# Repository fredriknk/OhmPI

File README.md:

# OhmPi

Development of a low-cost multi-electrodes resistivity meter for electrical resistivity mesaurement for lab applications, based on raspberry board

## Installation

All dependencies are specified in *requirements.txt*

**Note:** all instructions below should be typed in the terminal

It is first necessary to create an OhmPi virtual environment and install all dependancies
`.create_ohmpi_virtual_envrinment.sh`

When the installation is completed check that requirements are met using 
`pip list`

We strongly recommend users to create a virtual environment to run the code and installed all required dependencies:
*  activate it using the following command:
   `source ohmpy/bin/activate`
*  you should run you code within the virtual environment
*  to leave the virtual environment simply type: `deactivate`

## First run with four electrodes

In the examples folder, you will find the code "simple_measurement.py".

Running this code, in Thonny (IDE) or in the terminal, will allow you to make a simple 4 electrodes measurement A B M N.

## Citing Ohmpi

If you use Ohmpi for you work, please cite [this paper](https://www.sciencedirect.com/science/article/pii/S2468067220300316) as:

    Rémi Clement, Yannick Fargier, Vivien Dubois, Julien Gance, Emile Gros, Nicolas Forquet, OhmPi: An open source data logger for 
    dedicated applications of electrical resistivity imaging at the small and laboratory scale, HardwareX, Volume 8, 2020, e00122, ISSN 2468-0672, https://doi.org/10.1016/j.ohx.2020.e00122..

## License information

You may redistribute and modify this documentation and make products using it under the terms of the CERN-OHL-P v2 (https:/cern.ch/cern-ohl). This documentation is distributed WITHOUT ANY EXPRESS OR IMPLIED WARRANTY, INCLUDING OF MERCHANTABILITY, SATISFACTORY QUALITY AND FITNESS FOR A PARTICULAR PURPOSE. Please see the CERN-OHL-P v2 for applicable conditions

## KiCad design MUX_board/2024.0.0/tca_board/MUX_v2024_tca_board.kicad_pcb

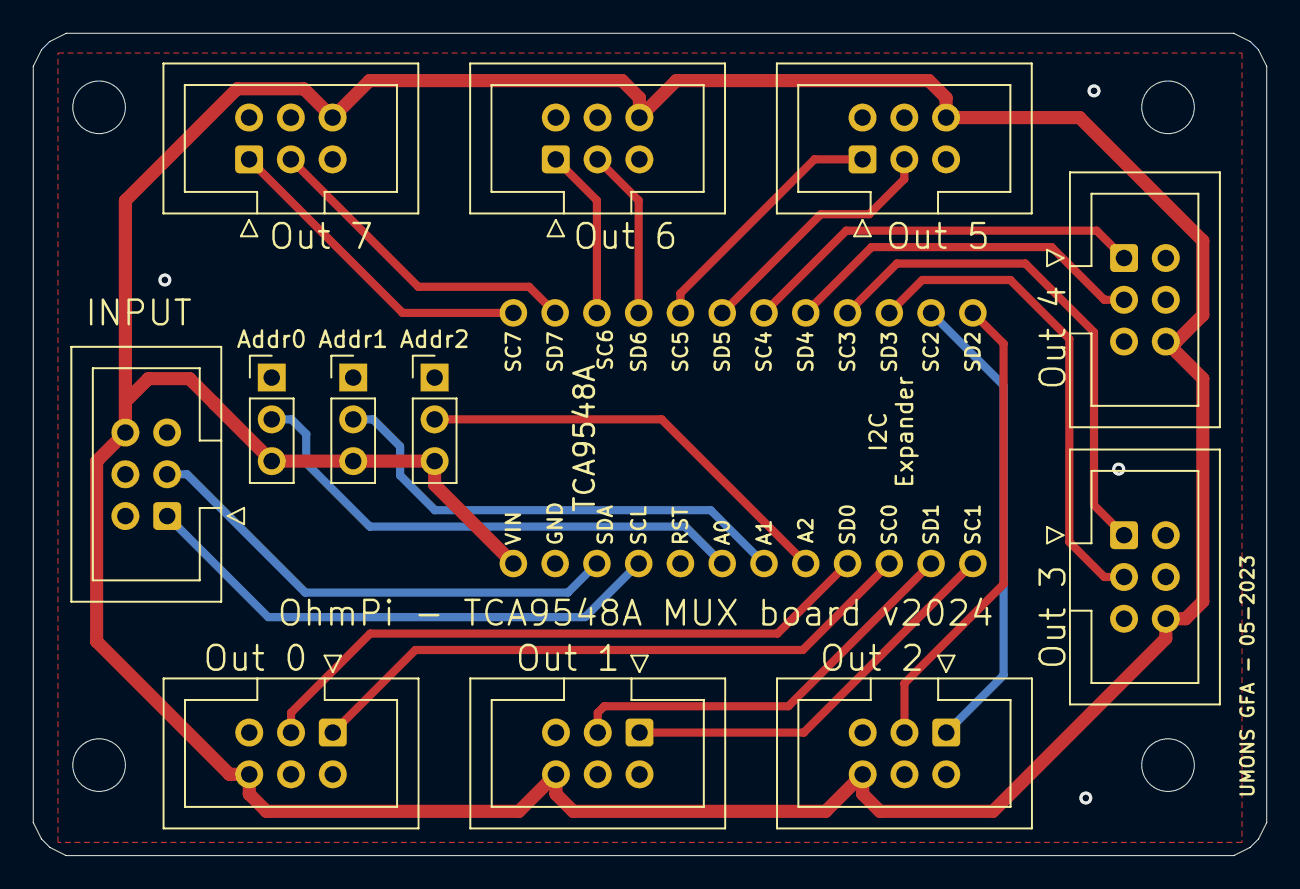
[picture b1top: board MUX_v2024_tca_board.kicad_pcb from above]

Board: 2 copper layers, 75.0 x 50.0 mm, 14 parts (0 on the bottom side), 23 nets.

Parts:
Addr0: Addr0; PinHeader_1x03_P2.54mm_Vertical
Addr1: Addr 1; PinHeader_1x03_P2.54mm_Vertical
Addr2: Addr 2; PinHeader_1x03_P2.54mm_Vertical
J1, J2, J3, J4, J5, J6, J7, J8, J9: I2C; IDC-Header_2x03_P2.54mm_Vertical
JP1, JP3: HEADER-1X12; 1X12_ROUND

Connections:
+5V: Addr0.3 (B), Addr1.3 (B), Addr2.3 (B), J1.6, J2.6, J3.6, J4.6, J5.6, J6.6, J7.6, J8.6, J9.6, JP3.1
/0SCL: J2.1, JP3.10
/0SDA: J2.3, JP3.9
/1SCL: J3.1, JP3.12
/1SDA: J3.3, JP3.11
/2SCL: J9.1, JP1.2
/2SDA: J9.3, JP1.1
/3SCL: J8.1, JP1.4
/3SDA: J8.3, JP1.3
/4SCL: J7.1, JP1.6
/4SDA: J7.3, JP1.5
/5SCL: J6.1, JP1.8
/5SDA: J6.3, JP1.7
/6SCL: J5.1, JP1.10
/6SDA: J5.3, JP1.9
/7SCL: J4.1, JP1.12
/7SDA: J4.3, JP1.11
/A0: Addr0.2 (C), JP3.6
/A1: Addr1.2 (C), JP3.7
/A2: Addr2.2 (C), JP3.8
/INPUTSCL: J1.1, JP3.4
/INPUTSDA: J1.3, JP3.3
GNDD: Addr0.1 (A), Addr1.1 (A), Addr2.1 (A), J1.5, J2.5, J3.5, J4.5, J5.5, J6.5, J7.5, J8.5, J9.5, JP3.2

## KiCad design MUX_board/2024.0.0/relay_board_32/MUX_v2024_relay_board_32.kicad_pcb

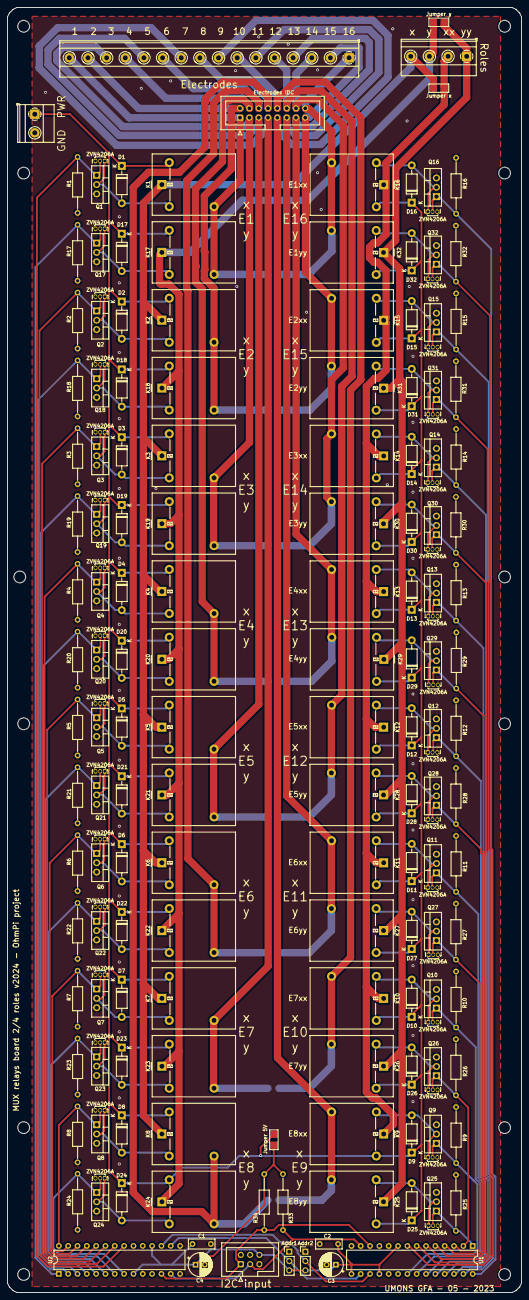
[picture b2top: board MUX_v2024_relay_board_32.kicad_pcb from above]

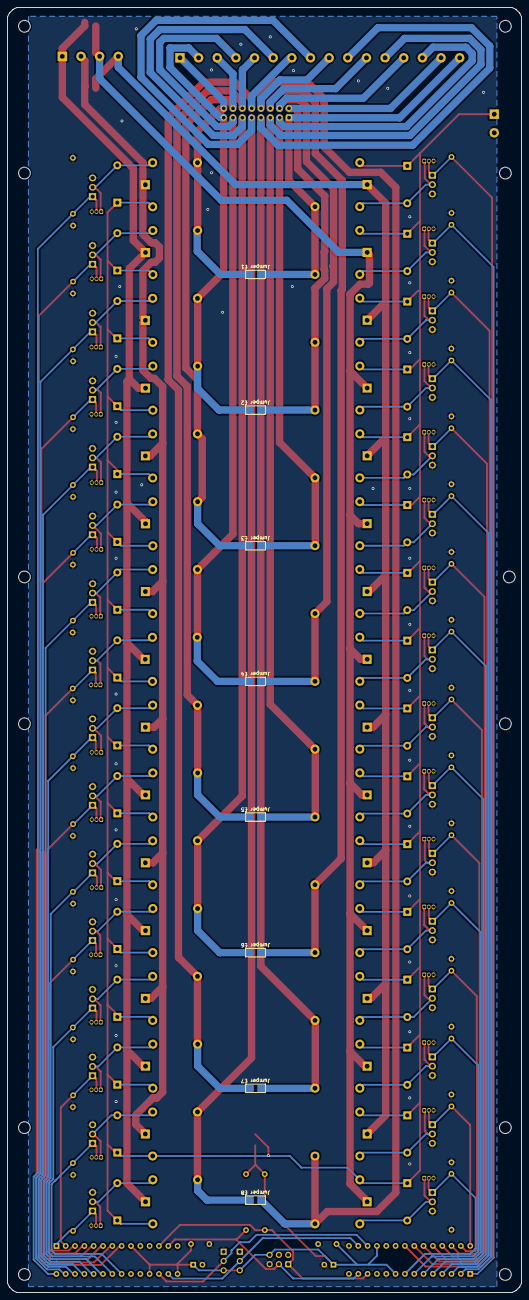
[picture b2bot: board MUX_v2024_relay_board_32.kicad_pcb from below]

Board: 2 copper layers, 140.0 x 350.0 mm, 186 parts (8 on the bottom side), 91 nets.

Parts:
Addr1: Addr 1; PinHeader_1x03_P2.54mm_Vertical
Addr2: Addr 2; PinHeader_1x03_P2.54mm_Vertical
C1, C2: 100nF; C_Disc_D7.0mm_W2.5mm_P5.00mm
C3, C4: 10uF; CP_Radial_D6.3mm_P2.50mm
D1, D2, D3, D4, D5, D6, D7, D8, D9, D10, D11, D12, D13, D14, D15, D16, D17, D18, D19, D20, D21, D22, D23, D24, D25, D26, D27, D28, D29, D30, D31, D32: 1N_E4007; D_DO-41_SOD81_P10.16mm_Horizontal
Electrodes: Screw_Terminal_01x16; TerminalBlock_Phoenix_MKDS-1,5-16-5.08_1x16_P5.08mm_Horizon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
Electrodes IDC: Conn_02x08_Odd_Even; IDC-Header_2x08_P2.54mm_Vertical
GND  PWR: Relays Pwr; TerminalBlock_Phoenix_MKDS-1,5-2-5.08_1x02_P5.08mm_Horizont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
I2C input: I2C; IDC-Header_2x03_P2.54mm_Vertical
Jumper 5V: SolderJumper_2_Open; Soder_jumper
Jumper E1, Jumper E2, Jumper E3, Jumper E4, Jumper E5, Jumper E6, Jumper E7, Jumper E8: SolderJumper_2_Open; Soder_jumper
Jumper x: SolderJumper_2_Open; Soder_jumper
Jumper y: SolderJumper_2_Open; Soder_jumper
K1, K2, K3, K4, K5, K6, K7, K8, K9, K10, K11, K12, K13, K14, K15, K16, K17, K18, K19, K20, K21, K22, K23, K24, K25, K26, K27, K28, K29, K30, K31, K32: G5LE-1-VD; Relay_SPDT_Omron-G5LE-1-VD
Q1, Q2, Q3, Q4, Q5, Q6, Q7, Q8, Q9, Q10, Q11, Q12, Q13, Q14, Q15, Q16, Q17, Q18, Q19, Q20, Q21, Q22, Q23, Q24, Q25, Q26, Q27, Q28, Q29, Q30, Q31, Q32: STP16NF06L; TO-220-3_Vertical
R1, R2, R3, R4, R5, R6, R7, R8, R9, R10, R11, R12, R13, R14, R15, R16, R17, R18, R19, R20, R21, R22, R23, R24, R25, R26, R27, R28, R29, R30, R31, R32, R33, R34: 100k; R_Axial_DIN0207_L6.3mm_D2.5mm_P15.24mm_Horizontal
U1, U2: MCP23017_SP; DIP-28_W7.62mm
ZVN4206A, ZVN4206A#2, ZVN4206A#3, ZVN4206A#4, ZVN4206A#5, ZVN4206A#6, ZVN4206A#7, ZVN4206A#8, ZVN4206A#9, ZVN4206A#10, ZVN4206A#11, ZVN4206A#12, ZVN4206A#13, ZVN4206A#14, ZVN4206A#15, ZVN4206A#16, ZVN4206A#17, ZVN4206A#18, ZVN4206A#19, ZVN4206A#20, ZVN4206A#21, ZVN4206A#22, ZVN4206A#23, ZVN4206A#24, ZVN4206A#25, ZVN4206A#26, ZVN4206A#27, ZVN4206A#28, ZVN4206A#29, ZVN4206A#30, ZVN4206A#31, ZVN4206A#32: TO-92Flat
x  y  xx yy: Screw_Terminal_01x04; TerminalBlock_Phoenix_MKDS-1,5-4-5.08_1x04_P5.08mm_Horizont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

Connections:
12V: D1.1 (K), D2.1 (K), D3.1 (K), D4.1 (K), D5.1 (K), D6.1 (K), D7.1 (K), D8.1 (K), D9.1 (K), D10.1 (K), D11.1 (K), D12.1 (K), D13.1 (K), D14.1 (K), D15.1 (K), D16.1 (K), D17.1 (K), D18.1 (K), D19.1 (K), D20.1 (K), D21.1 (K), D22.1 (K), D23.1 (K), D24.1 (K), D25.1 (K), D26.1 (K), D27.1 (K), D28.1 (K), D29.1 (K), D30.1 (K), D31.1 (K), D32.1 (K), GND PWR.1, Jumper 5V.2 (B), K1.5, K2.5, K3.5, K4.5, K5.5, K6.5, K7.5, K8.5, K9.5, K10.5, K11.5, K12.5, K13.5, K14.5, K15.5, K16.5, K17.5, K18.5, K19.5, K20.5, K21.5, K22.5, K23.5, K24.5, K25.5, K26.5, K27.5, K28.5, K29.5, K30.5, K31.5, K32.5
+5V: Addr1.3 (B), Addr2.3 (B), C1.1, C2.1, C3.1, C4.1, I2C input.6, Jumper 5V.1 (A), R33.1, R34.1, U1.9 (VDD), U1.15 (A0), U1.18 (~RESET), U2.9 (VDD), U2.18 (~RESET)
Addr1: Addr1.2 (C), U1.16 (A1), U2.16 (A1)
Addr2: Addr2.2 (C), U1.17 (A2), U2.17 (A2)
E1x: Q1.1 (G), R1.1, U2.21 (GPA0), ZVN4206A#27.2
E1y: Q17.1 (G), R17.1, U2.1 (GPB0), ZVN4206A#7.2
E2x: Q2.1 (G), R2.1, U2.22 (GPA1), ZVN4206A#6.2
E2y: Q18.1 (G), R18.1, U2.2 (GPB1), ZVN4206A#32.2
E3x: Q3.1 (G), R3.1, U2.23 (GPA2), ZVN4206A#31.2
E3y: Q19.1 (G), R19.1, U2.3 (GPB2), ZVN4206A#9.2
E4x: Q4.1 (G), R4.1, U2.24 (GPA3), ZVN4206A#5.2
E4y: Q20.1 (G), R20.1, U2.4 (GPB3), ZVN4206A#12.2
E5x: Q5.1 (G), R5.1, U2.25 (GPA4), ZVN4206A#26.2
E5y: Q21.1 (G), R21.1, U2.5 (GPB4), ZVN4206A#8.2
E6x: Q6.1 (G), R6.1, U2.26 (GPA5), ZVN4206A#22.2
E6y: Q22.1 (G), R22.1, U2.6 (GPB5), ZVN4206A#11.2
E7x: Q7.1 (G), R7.1, U2.27 (GPA6), ZVN4206A#17.2
E7y: Q23.1 (G), R23.1, U2.7 (GPB6), ZVN4206A#30.2
E8x: Q8.1 (G), R8.1, U2.28 (GPA7), ZVN4206A#2.2
E8y: Q24.1 (G), R24.1, U2.8 (GPB7), ZVN4206A#21.2
E9x: Q9.1 (G), R9.1, U1.21 (GPA0), ZVN4206A#24.2
E9y: Q25.1 (G), R25.1, U1.1 (GPB0), ZVN4206A#28.2
E10x: Q10.1 (G), R10.1, U1.22 (GPA1), ZVN4206A#25.2
E10y: Q26.1 (G), R26.1, U1.2 (GPB1), ZVN4206A#20.2
E11x: Q11.1 (G), R11.1, U1.23 (GPA2), ZVN4206A.2
E11y: Q27.1 (G), R27.1, U1.3 (GPB2), ZVN4206A#10.2
E12x: Q12.1 (G), R12.1, U1.24 (GPA3), ZVN4206A#18.2
E12y: Q28.1 (G), R28.1, U1.4 (GPB3), ZVN4206A#29.2
E13x: Q13.1 (G), R13.1, U1.25 (GPA4), ZVN4206A#13.2
E13y: Q29.1 (G), R29.1, U1.5 (GPB4), ZVN4206A#19.2
E14x: Q14.1 (G), R14.1, U1.26 (GPA5), ZVN4206A#16.2
E14y: Q30.1 (G), R30.1, U1.6 (GPB5), ZVN4206A#14.2
E15x: Q15.1 (G), R15.1, U1.27 (GPA6), ZVN4206A#4.2
E15y: Q31.1 (G), R31.1, U1.7 (GPB6), ZVN4206A#3.2
E16x: Q16.1 (G), R16.1, U1.28 (GPA7), ZVN4206A#15.2
E16y: Q32.1 (G), R32.1, U1.8 (GPB7), ZVN4206A#23.2
Electrode 1: Electrodes.16, Electrodes IDC.1, Jumper E1.1 (A), K1.3, K17.3
Electrode 2: Electrodes.15, Electrodes IDC.2, Jumper E2.1 (A), K2.3, K18.3
Electrode 3: Electrodes.14, Electrodes IDC.3, Jumper E3.1 (A), K3.3, K19.3
Electrode 4: Electrodes.13, Electrodes IDC.4, Jumper E4.1 (A), K4.3, K20.3
Electrode 5: Electrodes.12, Electrodes IDC.5, Jumper E5.1 (A), K5.3, K21.3
Electrode 6: Electrodes.11, Electrodes IDC.6, Jumper E6.1 (A), K6.3, K22.3
Electrode 7: Electrodes.10, Electrodes IDC.7, Jumper E7.1 (A), K7.3, K23.3
Electrode 8: Electrodes.9, Electrodes IDC.8, Jumper E8.1 (A), K8.3, K24.3
Electrode 9: Electrodes.8, Electrodes IDC.9, Jumper E8.2 (B), K9.3, K25.3
Electrode 10: Electrodes.7, Electrodes IDC.10, Jumper E7.2 (B), K10.3, K26.3
Electrode 11: Electrodes.6, Electrodes IDC.11, Jumper E6.2 (B), K11.3, K27.3
Electrode 12: Electrodes.5, Electrodes IDC.12, Jumper E5.2 (B), K12.3, K28.3
Electrode 13: Electrodes.4, Electrodes IDC.13, Jumper E4.2 (B), K13.3, K29.3
Electrode 14: Electrodes.3, Electrodes IDC.14, Jumper E3.2 (B), K14.3, K30.3
Electrode 15: Electrodes.2, Electrodes IDC.15, Jumper E2.2 (B), K15.3, K31.3
Electrode 16: Electrodes.1, Electrodes IDC.16, Jumper E1.2 (B), K16.3, K32.3
GND: Addr1.1 (A), Addr2.1 (A), C1.2, C2.2, C3.2, C4.2, GND PWR.2, I2C input.5, Q1.3 (S), Q2.3 (S), Q3.3 (S), Q4.3 (S), Q5.3 (S), Q6.3 (S), Q7.3 (S), Q8.3 (S), Q9.3 (S), Q10.3 (S), Q11.3 (S), Q12.3 (S), Q13.3 (S), Q14.3 (S), Q15.3 (S), Q16.3 (S), Q17.3 (S), Q18.3 (S), Q19.3 (S), Q20.3 (S), Q21.3 (S), Q22.3 (S), Q23.3 (S), Q24.3 (S), Q25.3 (S), Q26.3 (S), Q27.3 (S), Q28.3 (S), Q29.3 (S), Q30.3 (S), Q31.3 (S), Q32.3 (S), R1.2, R2.2, R3.2, R4.2, R5.2, R6.2, R7.2, R8.2, R9.2, R10.2, R11.2, R12.2, R13.2, R14.2, R15.2, R16.2, R17.2, R18.2, R19.2, R20.2, R21.2, R22.2, R23.2, R24.2, R25.2, R26.2, R27.2, R28.2, R29.2, R30.2, R31.2, R32.2, U1.10 (VSS), U2.10 (VSS), U2.15 (A0), ZVN4206A.3, ZVN4206A#2.3, ZVN4206A#3.3, ZVN4206A#4.3, ZVN4206A#5.3, ZVN4206A#6.3, ZVN4206A#7.3, ZVN4206A#8.3, ZVN4206A#9.3, ZVN4206A#10.3, ZVN4206A#11.3, ZVN4206A#12.3, ZVN4206A#13.3, ZVN4206A#14.3, ZVN4206A#15.3, ZVN4206A#16.3, ZVN4206A#17.3, ZVN4206A#18.3, ZVN4206A#19.3, ZVN4206A#20.3, ZVN4206A#21.3, ZVN4206A#22.3, ZVN4206A#23.3, ZVN4206A#24.3, ZVN4206A#25.3, ZVN4206A#26.3, ZVN4206A#27.3, ZVN4206A#28.3, ZVN4206A#29.3, ZVN4206A#30.3, ZVN4206A#31.3, ZVN4206A#32.3
unnamed: D1.2 (A), K1.2, Q1.2 (D), ZVN4206A#27.1
unnamed: D2.2 (A), K2.2, Q2.2 (D), ZVN4206A#6.1
unnamed: D3.2 (A), K3.2, Q3.2 (D), ZVN4206A#31.1
unnamed: D4.2 (A), K4.2, Q4.2 (D), ZVN4206A#5.1
unnamed: D5.2 (A), K5.2, Q5.2 (D), ZVN4206A#26.1
unnamed: D6.2 (A), K6.2, Q6.2 (D), ZVN4206A#22.1
unnamed: D7.2 (A), K7.2, Q7.2 (D), ZVN4206A#17.1
unnamed: D8.2 (A), K8.2, Q8.2 (D), ZVN4206A#2.1
unnamed: D9.2 (A), K9.2, Q9.2 (D), ZVN4206A#24.1
unnamed: D10.2 (A), K10.2, Q10.2 (D), ZVN4206A#25.1
unnamed: D11.2 (A), K11.2, Q11.2 (D), ZVN4206A.1
unnamed: D12.2 (A), K12.2, Q12.2 (D), ZVN4206A#18.1
unnamed: D13.2 (A), K13.2, Q13.2 (D), ZVN4206A#13.1
unnamed: D14.2 (A), K14.2, Q14.2 (D), ZVN4206A#16.1
unnamed: D15.2 (A), K15.2, Q15.2 (D), ZVN4206A#4.1
unnamed: D16.2 (A), K16.2, Q16.2 (D), ZVN4206A#15.1
unnamed: D17.2 (A), K17.2, Q17.2 (D), ZVN4206A#7.1
unnamed: D18.2 (A), K18.2, Q18.2 (D), ZVN4206A#32.1
unnamed: D19.2 (A), K19.2, Q19.2 (D), ZVN4206A#9.1
unnamed: D20.2 (A), K20.2, Q20.2 (D), ZVN4206A#12.1
unnamed: D21.2 (A), K21.2, Q21.2 (D), ZVN4206A#8.1
unnamed: D22.2 (A), K22.2, Q22.2 (D), ZVN4206A#11.1
unnamed: D23.2 (A), K23.2, Q23.2 (D), ZVN4206A#30.1
unnamed: D24.2 (A), K24.2, Q24.2 (D), ZVN4206A#21.1
unnamed: D25.2 (A), K25.2, Q25.2 (D), ZVN4206A#28.1
unnamed: D26.2 (A), K26.2, Q26.2 (D), ZVN4206A#20.1
unnamed: D27.2 (A), K27.2, Q27.2 (D), ZVN4206A#10.1
unnamed: D28.2 (A), K28.2, Q28.2 (D), ZVN4206A#29.1
unnamed: D29.2 (A), K29.2, Q29.2 (D), ZVN4206A#19.1
unnamed: D30.2 (A), K30.2, Q30.2 (D), ZVN4206A#14.1
unnamed: D31.2 (A), K31.2, Q31.2 (D), ZVN4206A#3.1
unnamed: D32.2 (A), K32.2, Q32.2 (D), ZVN4206A#23.1
Role x: Jumper x.1 (A), K1.1, K2.1, K3.1, K4.1, K5.1, K6.1, K7.1, K8.1, x y xx yy.4
Role xx: Jumper x.2 (B), K9.1, K10.1, K11.1, K12.1, K13.1, K14.1, K15.1, K16.1, x y xx yy.2
Role y: Jumper y.1 (A), K17.1, K18.1, K19.1, K20.1, K21.1, K22.1, K23.1, K24.1, x y xx yy.3
Role yy: Jumper y.2 (B), K25.1, K26.1, K27.1, K28.1, K29.1, K30.1, K31.1, K32.1, x y xx yy.1
SCL1: I2C input.1, R34.2, U1.12 (SCK), U2.12 (SCK)
SD1: I2C input.3, R33.2, U1.13 (SDA), U2.13 (SDA)

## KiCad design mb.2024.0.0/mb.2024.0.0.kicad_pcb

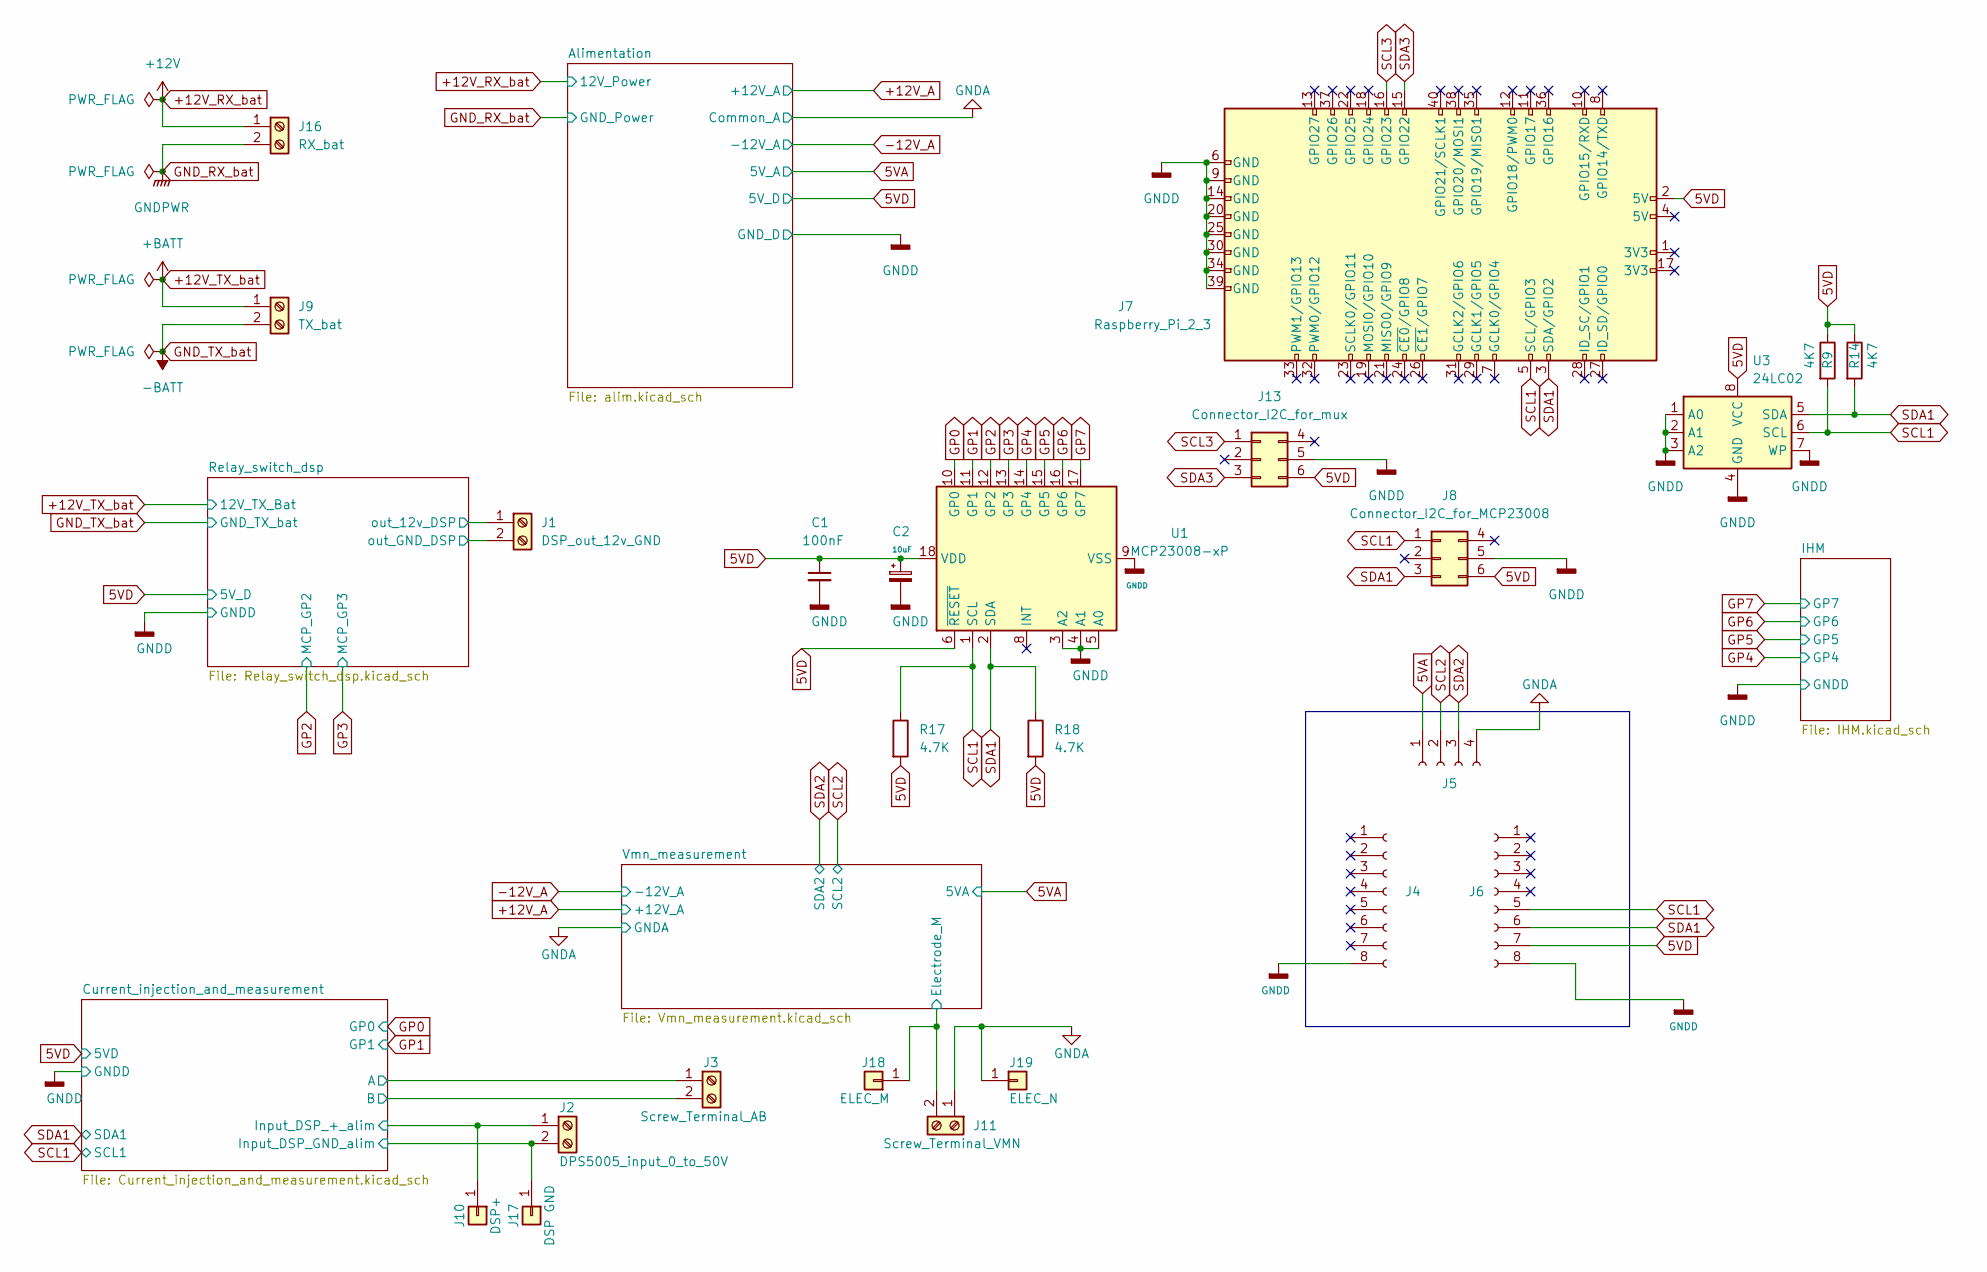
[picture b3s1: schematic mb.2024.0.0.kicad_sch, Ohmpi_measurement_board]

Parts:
C1: 100nF; C_Disc_D8.0mm_W2.5mm_P5.00mm
C2: 10uF; CP_Radial_D6.3mm_P2.50mm
J1: DSP_out_12v_GND; TerminalBlock_Phoenix_MKDS-1,5-2-5.08_1x02_P5.08mm_Horizont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
J2: DPS5005_input_0_to_50V; TerminalBlock_Phoenix_MKDS-1,5-2-5.08_1x02_P5.08mm_Horizont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
J3: Screw_Terminal_AB; TerminalBlock_Phoenix_MKDS-1,5-2-5.08_1x02_P5.08mm_Horizont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
J4, J6: Conn_01x08_Female; PinHeader_1x08_P2.54mm_Vertical
J5: Conn_01x04_Female; PinHeader_1x04_P2.54mm_Vertical
J7: Raspberry_Pi_2_3; PinSocket_2x20_P2.54mm_Vertical
J8: Connector_I2C_for_MCP23008; IDC-Header_2x03_P2.54mm_Vertical
J9: TX_bat; TerminalBlock_Phoenix_MKDS-1,5-2-5.08_1x02_P5.08mm_Horizont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
J10: DSP+; PinHeader_1x01_P2.54mm_Vertical
J11: Screw_Terminal_VMN; TerminalBlock_Phoenix_MKDS-1,5-2-5.08_1x02_P5.08mm_Horizont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
J13: Connector_I2C_for_mux; IDC-Header_2x03_P2.54mm_Vertical
J16: RX_bat; TerminalBlock_Phoenix_MKDS-1,5-2-5.08_1x02_P5.08mm_Horizont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
J17: DSP GND; PinHeader_1x01_P2.54mm_Vertical
J18: ELEC_M; PinHeader_1x01_P2.54mm_Vertical
J19: ELEC_N; PinHeader_1x01_P2.54mm_Vertical
R9, R14: 4K7; R_Axial_DIN0204_L3.6mm_D1.6mm_P7.62mm_Horizontal
R17, R18: 4.7K; R_Axial_DIN0207_L6.3mm_D2.5mm_P7.62mm_Horizontal
U1: MCP23008-xP; DIP-18_W7.62mm
U3: 24LC02; DIP-8_W7.62mm

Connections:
5VA: J5.1; also elsewhere on the board
5VD: C1.1, C2.1, J6.7, J7.2 (5V), J8.6, J13.6, R9.1, R14.1, R17.2, R18.2, U1.6 (~RESET), U1.18 (VDD), U3.8 (VCC); also elsewhere on the board
+12V_RX_bat: J16.1; also elsewhere on the board
+12V_TX_bat: J9.1; also elsewhere on the board
/Current_injection_and_measurement/A: J3.1; also elsewhere on the board
/Current_injection_and_measurement/B: J3.2; also elsewhere on the board
/Current_injection_and_measurement/Input_DSP_+_alim: J2.1, J10.1; also elsewhere on the board
/Current_injection_and_measurement/Input_DSP_GND_alim: J2.2, J17.1; also elsewhere on the board
/Relay_switch_dsp/out_12v_DSP: J1.1; also elsewhere on the board
/Relay_switch_dsp/out_GND_DSP: J1.2; also elsewhere on the board
/Vmn_measurement/Electrode_M: J11.2, J18.1; also elsewhere on the board
GNDA: J5.4, J11.1, J19.1; also elsewhere on the board
GNDD: C1.2, C2.2, J4.8, J6.8, J7.6 (GND), J7.9 (GND), J7.14 (GND), J7.20 (GND), J7.25 (GND), J7.30 (GND), J7.34 (GND), J7.39 (GND), J8.5, J13.5, U1.3 (A2), U1.4 (A1), U1.5 (A0), U1.9 (VSS), U3.1 (A0), U3.2 (A1), U3.3 (A2), U3.4 (GND), U3.7 (WP); also elsewhere on the board
GND_RX_bat: J16.2; also elsewhere on the board
GND_TX_bat: J9.2; also elsewhere on the board
GP0: U1.10 (GP0); also elsewhere on the board
GP1: U1.11 (GP1); also elsewhere on the board
GP2: U1.12 (GP2); also elsewhere on the board
GP3: U1.13 (GP3); also elsewhere on the board
GP4: U1.14 (GP4); also elsewhere on the board
GP5: U1.15 (GP5); also elsewhere on the board
GP6: U1.16 (GP6); also elsewhere on the board
GP7: U1.17 (GP7); also elsewhere on the board
SCL1: J6.5, J7.5 (SCL/GPIO3), J8.1, R9.2, R17.1, U1.1 (SCL), U3.6 (SCL); also elsewhere on the board
SCL2: J5.2; also elsewhere on the board
SCL3: J7.16 (GPIO23), J13.1
SDA1: J6.6, J7.3 (SDA/GPIO2), J8.3, R14.2, R18.1, U1.2 (SDA), U3.5 (SDA); also elsewhere on the board
SDA2: J5.3; also elsewhere on the board
SDA3: J7.15 (GPIO22), J13.3

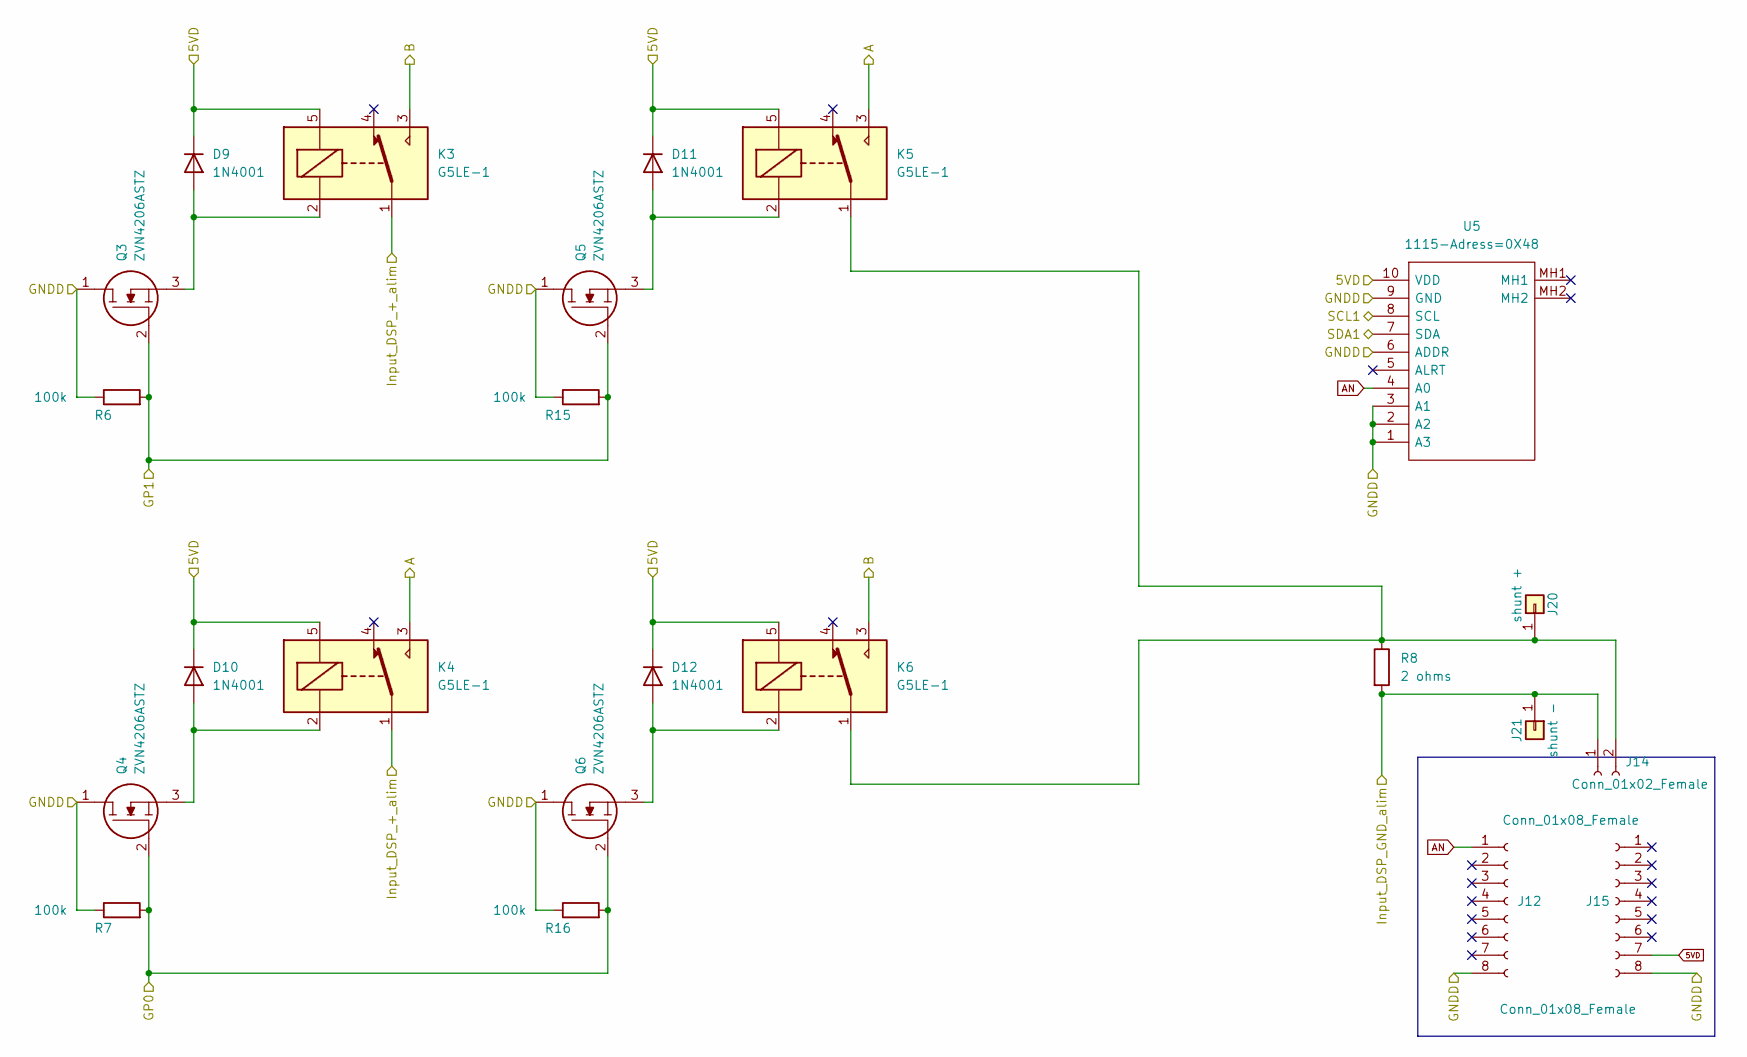
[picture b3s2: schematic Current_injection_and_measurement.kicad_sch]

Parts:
D9, D10, D11, D12: 1N4001; D_DO-41_SOD81_P10.16mm_Horizontal
J12, J15: Conn_01x08_Female; PinHeader_1x08_P2.54mm_Vertical
J14: Conn_01x02_Female; PinHeader_1x02_P2.54mm_Vertical
J20: shunt +; PinHeader_1x01_P2.54mm_Vertical
J21: shunt -; PinHeader_1x01_P2.54mm_Vertical
K3, K4, K5, K6: G5LE-1; Relay_SPDT_Omron-G5LE-1
Q3, Q4, Q5, Q6: ZVN4206ASTZ; TO-92L_Wide; Manufacturer_Part_Number ZVN4206ASTZ; Mouser Part Number 522-ZVN4206ASTZ
R6, R7, R15, R16: 100k; R_Axial_DIN0207_L6.3mm_D2.5mm_P7.62mm_Horizontal
R8: 2 ohms; R_Axial_DIN0414_L11.9mm_D4.5mm_P20.32mm_Horizontal
U5: 1115-Adress=0X48; 1085; PARTREV N/A; Mouser Part Number 485-1085

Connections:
5VD: D9.1 (K), D10.1 (K), D11.1 (K), D12.1 (K), J15.7, K3.5, K4.5, K5.5, K6.5, U5.10 (VDD); also elsewhere on the board
/Current_injection_and_measurement/A: K4.3, K5.3; also elsewhere on the board
/Current_injection_and_measurement/B: K3.3, K6.3; also elsewhere on the board
/Current_injection_and_measurement/Input_DSP_+_alim: K3.1, K4.1; also elsewhere on the board
/Current_injection_and_measurement/Input_DSP_GND_alim: J14.1, J21.1, R8.2; also elsewhere on the board
AN: J12.1, U5.4 (A0)
GNDD: J12.8, J15.8, Q3.1, Q4.1, Q5.1, Q6.1, R6.1, R7.1, R15.1, R16.1, U5.1 (A3), U5.2 (A2), U5.3 (A1), U5.6 (ADDR), U5.9 (GND); also elsewhere on the board
GP0: Q4.2, Q6.2, R7.2, R16.2; also elsewhere on the board
GP1: Q3.2, Q5.2, R6.2, R15.2; also elsewhere on the board
unnamed: D9.2 (A), K3.2, Q3.3
unnamed: D10.2 (A), K4.2, Q4.3
unnamed: D11.2 (A), K5.2, Q5.3
unnamed: D12.2 (A), K6.2, Q6.3
unnamed: J14.2, J20.1, K5.1, K6.1, R8.1
SCL1: U5.8 (SCL); also elsewhere on the board
SDA1: U5.7 (SDA); also elsewhere on the board

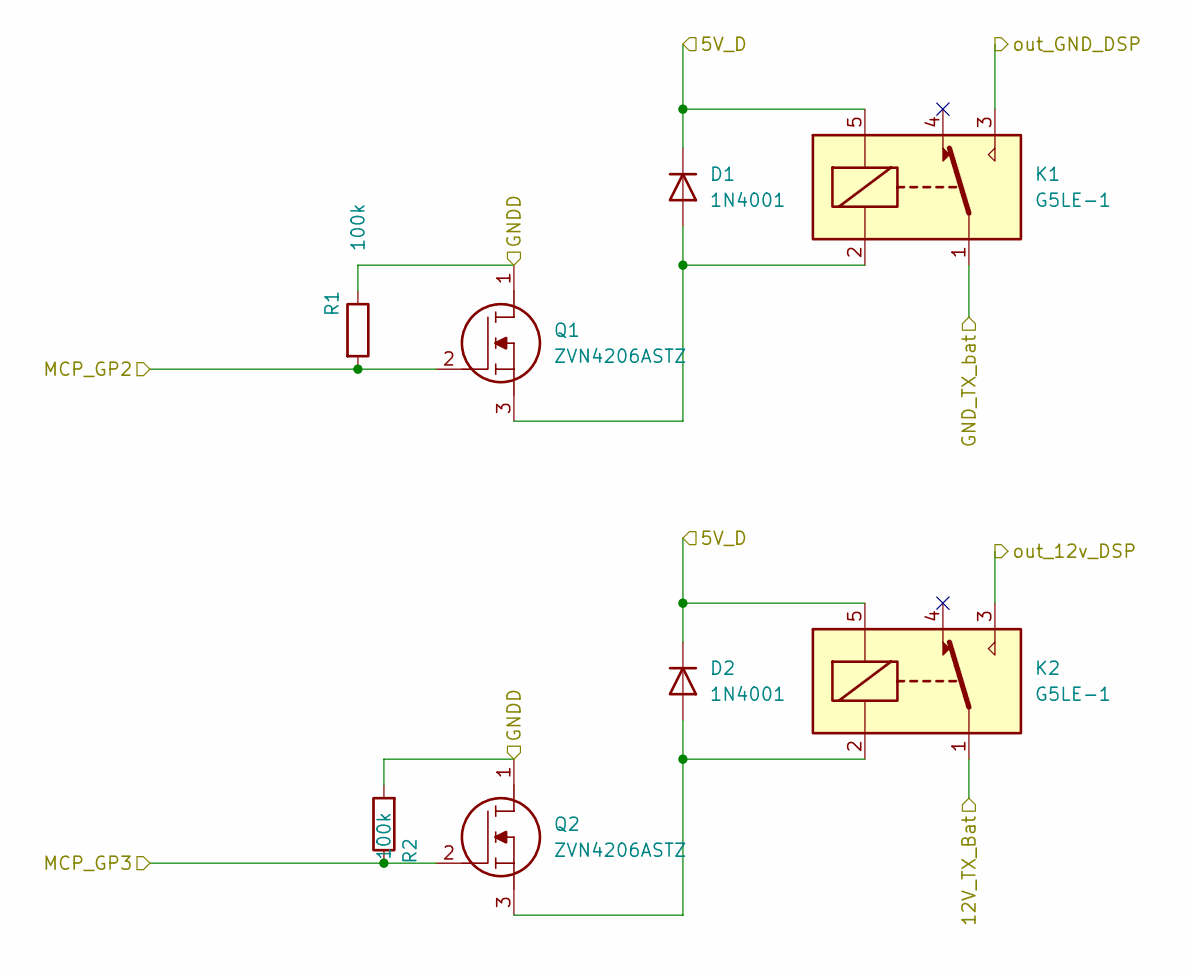
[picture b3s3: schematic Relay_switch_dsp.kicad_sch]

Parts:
D1, D2: 1N4001; D_DO-41_SOD81_P10.16mm_Horizontal
K1, K2: G5LE-1; Relay_SPDT_Omron-G5LE-1
Q1, Q2: ZVN4206ASTZ; TO-92L_Wide; Manufacturer_Part_Number ZVN4206ASTZ; Mouser Part Number 522-ZVN4206ASTZ
R1, R2: 100k; R_Axial_DIN0207_L6.3mm_D2.5mm_P7.62mm_Horizontal

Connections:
5VD: D1.1 (K), D2.1 (K), K1.5, K2.5; also elsewhere on the board
+12V_TX_bat: K2.1; also elsewhere on the board
/Relay_switch_dsp/out_12v_DSP: K2.3; also elsewhere on the board
/Relay_switch_dsp/out_GND_DSP: K1.3; also elsewhere on the board
GNDD: Q1.1, Q2.1, R1.1, R2.2; also elsewhere on the board
GND_TX_bat: K1.1; also elsewhere on the board
GP2: Q1.2, R1.2; also elsewhere on the board
GP3: Q2.2, R2.1; also elsewhere on the board
unnamed: D1.2 (A), K1.2, Q1.3
unnamed: D2.2 (A), K2.2, Q2.3

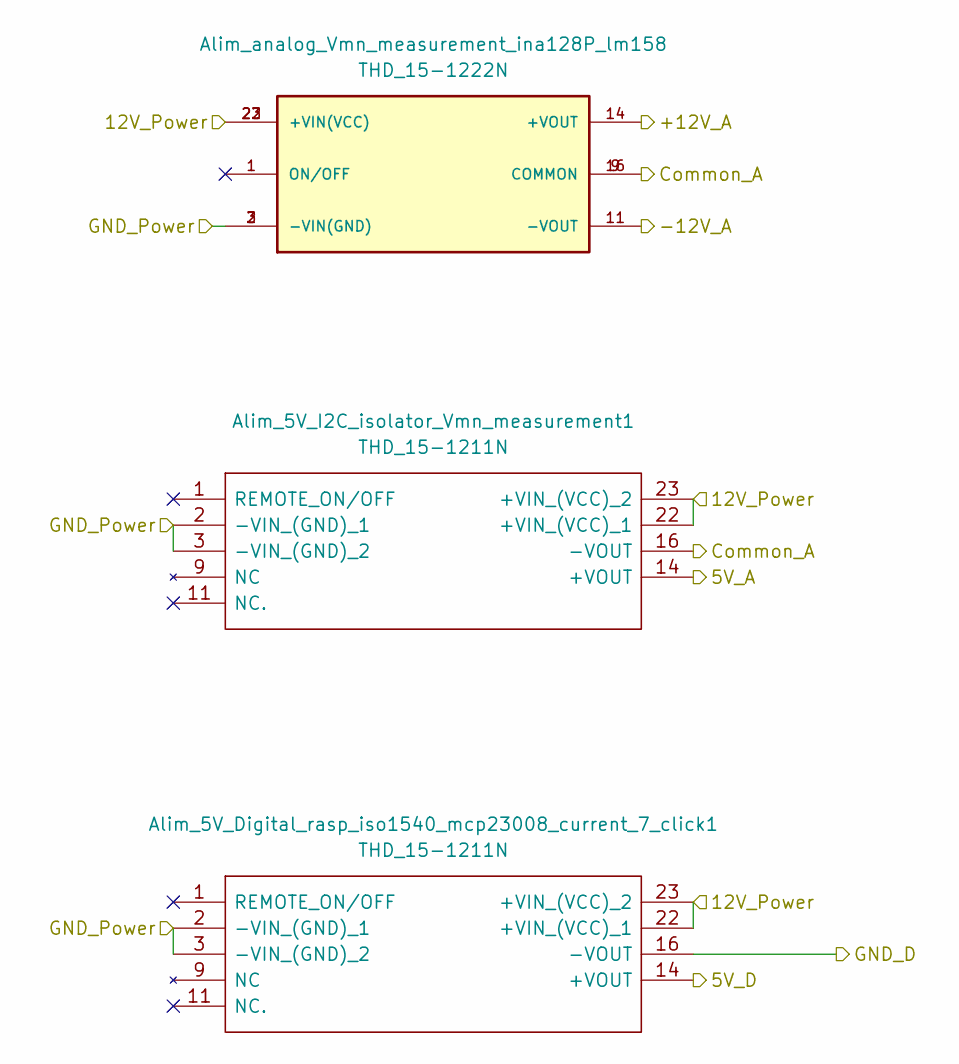
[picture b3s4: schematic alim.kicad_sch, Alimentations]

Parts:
Alim_5V_Digital_rasp_iso1540_mcp23008_current_7_click1, Alim_5V_I2C_isolator_Vmn_measurement1: THD_15-1211N; THD151211N; Manufacturer_Part_Number THD 15-1211N; Mouser Part Number 495-THD15-1211N
Alim_analog_Vmn_measurement_ina128P_lm158: THD_15-1222N; CONV_THD_15-1222N; PARTREV July 27, 2020

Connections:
5VA: Alim_5V_I2C_isolator_Vmn_measurement1.14 (+VOUT); also elsewhere on the board
5VD: Alim_5V_Digital_rasp_iso1540_mcp23008_c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.14 (+VOUT); also elsewhere on the board
+12V_A: Alim_analog_Vmn_measurement_ina128P_lm1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.14 (+VOUT); also elsewhere on the board
+12V_RX_bat: Alim_5V_Digital_rasp_iso1540_mcp23008_c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.22 (+VIN_(VCC)_1), Alim_5V_Digital_rasp_iso1540_mcp23008_c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.23 (+VIN_(VCC)_2), Alim_5V_I2C_isolator_Vmn_measurement1.22 (+VIN_(VCC)_1), Alim_5V_I2C_isolator_Vmn_measurement1.23 (+VIN_(VCC)_2), Alim_analog_Vmn_measurement_ina128P_lm1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.22 (+VIN(VCC)), Alim_analog_Vmn_measurement_ina128P_lm1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.23 (+VIN(VCC)); also elsewhere on the board
-12V_A: Alim_analog_Vmn_measurement_ina128P_lm1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.11 (-VOUT); also elsewhere on the board
GNDA: Alim_5V_I2C_isolator_Vmn_measurement1.16 (-VOUT), Alim_analog_Vmn_measurement_ina128P_lm1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.9 (COMMON), Alim_analog_Vmn_measurement_ina128P_lm1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.16 (COMMON); also elsewhere on the board
GNDD: Alim_5V_Digital_rasp_iso1540_mcp23008_c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.16 (-VOUT); also elsewhere on the board
GND_RX_bat: Alim_5V_Digital_rasp_iso1540_mcp23008_c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.2 (-VIN_(GND)_1), Alim_5V_Digital_rasp_iso1540_mcp23008_c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.3 (-VIN_(GND)_2), Alim_5V_I2C_isolator_Vmn_measurement1.2 (-VIN_(GND)_1), Alim_5V_I2C_isolator_Vmn_measurement1.3 (-VIN_(GND)_2), Alim_analog_Vmn_measurement_ina128P_lm1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.2 (-VIN(GND)), Alim_analog_Vmn_measurement_ina128P_lm1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.3 (-VIN(GND)); also elsewhere on the board

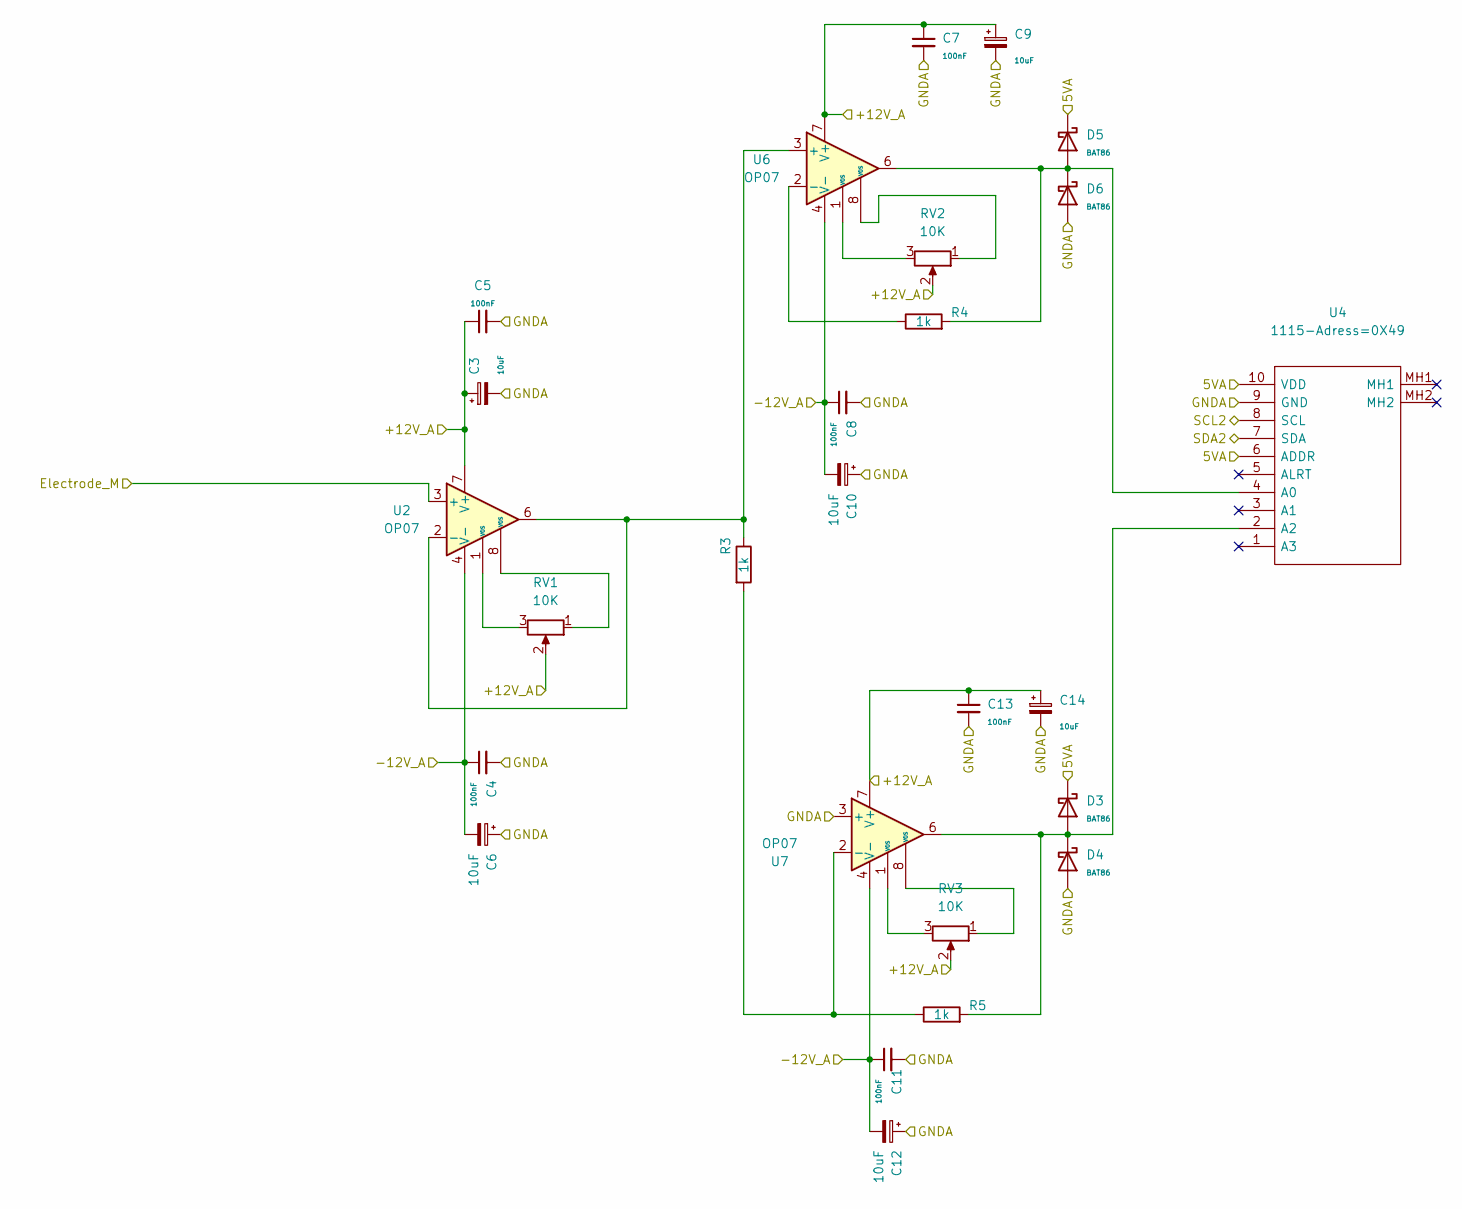
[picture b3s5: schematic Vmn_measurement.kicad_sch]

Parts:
C3, C6, C9, C10, C12, C14: 10uF; CP_Radial_D6.3mm_P2.50mm
C4, C5, C7, C8, C11, C13: 100nF; C_Disc_D8.0mm_W2.5mm_P5.00mm
D3, D4, D5, D6: BAT86; D_DO-35_SOD27_P7.62mm_Horizontal
R3, R4, R5: 1k; R_Axial_DIN0207_L6.3mm_D2.5mm_P7.62mm_Horizontal
RV1, RV2, RV3: 10K; Potentiometer_Bourns_3296W_Vertical
U2, U6, U7: OP07; DIP-8_W7.62mm
U4: 1115-Adress=0X49; 1085; PARTREV N/A; Mouser Part Number 485-1085

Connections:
5VA: D3.1 (K), D5.1 (K), U4.6 (ADDR), U4.10 (VDD); also elsewhere on the board
+12V_A: C3.1, C5.1, C7.1, C9.1, C13.1, C14.1, RV1.2, RV2.2, RV3.2, U2.7 (V+), U6.7 (V+), U7.7 (V+); also elsewhere on the board
-12V_A: C4.1, C6.2, C8.1, C10.2, C11.1, C12.2, U2.4 (V-), U6.4 (V-), U7.4 (V-); also elsewhere on the board
/Vmn_measurement/Electrode_M: U2.3 (+); also elsewhere on the board
GNDA: C3.2, C4.2, C5.2, C6.1, C7.2, C8.2, C9.2, C10.1, C11.2, C12.1, C13.2, C14.2, D4.2 (A), D6.2 (A), U4.9 (GND), U7.3 (+); also elsewhere on the board
unnamed: D3.2 (A), D4.1 (K), R5.2, U4.2 (A2), U7.6
unnamed: D5.2 (A), D6.1 (K), R4.2, U4.4 (A0), U6.6
unnamed: R3.1, U2.2 (-), U2.6, U6.3 (+)
unnamed: R3.2, R5.1, U7.2 (-)
unnamed: R4.1, U6.2 (-)
unnamed: RV1.1, U2.8 (VOS)
unnamed: RV1.3, U2.1 (VOS)
unnamed: RV2.1, U6.8 (VOS)
unnamed: RV2.3, U6.1 (VOS)
unnamed: RV3.1, U7.8 (VOS)
unnamed: RV3.3, U7.1 (VOS)
SCL2: U4.8 (SCL); also elsewhere on the board
SDA2: U4.7 (SDA); also elsewhere on the board
